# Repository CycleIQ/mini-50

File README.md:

# mini-50
A small 50A 48V e-bike controller

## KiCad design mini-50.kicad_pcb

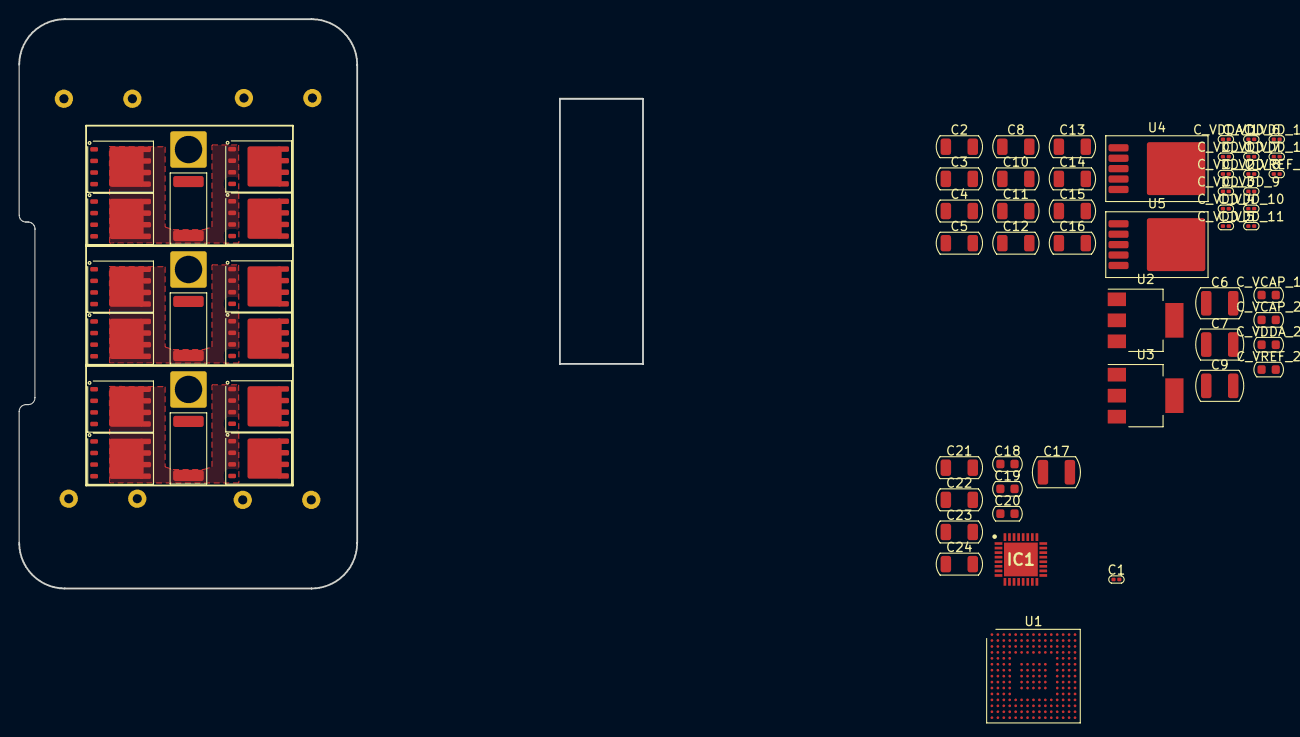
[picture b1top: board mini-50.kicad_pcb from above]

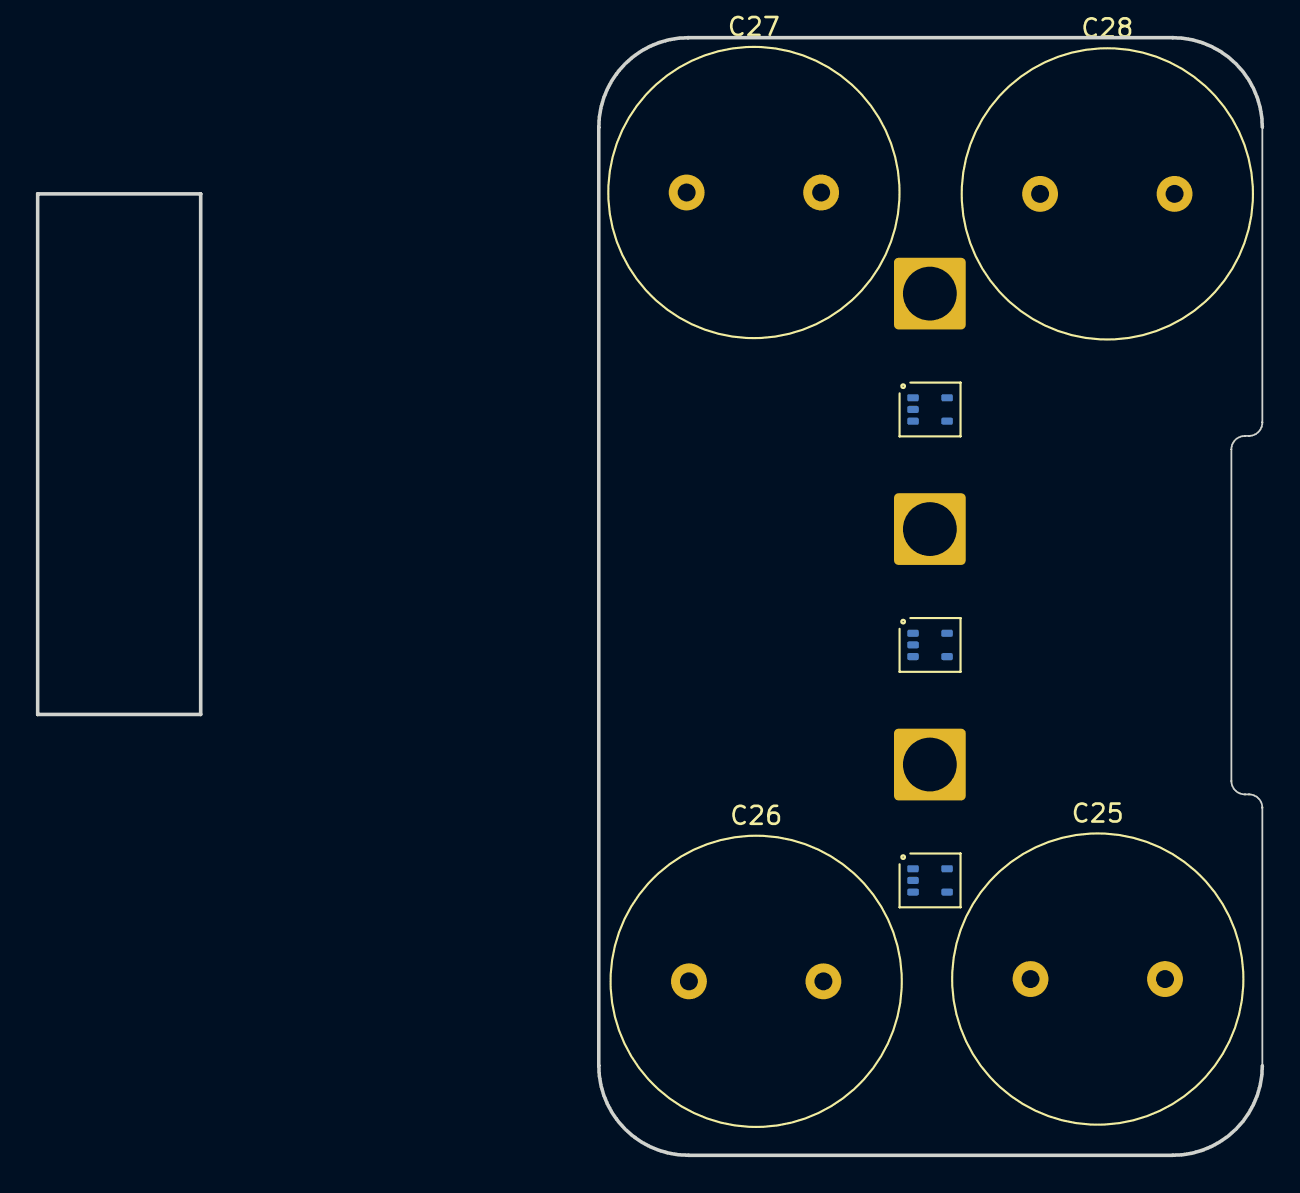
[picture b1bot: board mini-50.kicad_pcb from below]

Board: 4 copper layers, 74 parts (7 on the bottom side), 30 nets, no tracks yet.

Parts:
C1: 100nF; C_0201_0603Metric
C2, C5, C8, C10, C11, C12, C13, C14, C15, C16: 22uF/25V; C_1206_3216Metric
C3, C4: 4.7uF; C_1206_3216Metric
C6, C7, C9, C17: 10uF/100V; C_1210_3225Metric
C18: 1nF; C_0603_1608Metric
C19: 1uF; C_0603_1608Metric
C20: 10nF/25V; C_0603_1608Metric
C21: 10uF/25V; C_1206_3216Metric
C22, C23, C24: 2.2uF; C_1206_3216Metric
C25, C26, C27, C28: 680uF; C_Radial_D16.0mm_H25.0mm_P7.50mm
C_VCAP_1, C_VCAP_2: 2.2uF; C_0603_1608Metric
C_VDDA_1: 100nF; C_0201_0603Metric
C_VDDA_2: 1uF; C_0603_1608Metric
C_VDD_1, C_VDD_2, C_VDD_3, C_VDD_4, C_VDD_5, C_VDD_6, C_VDD_7, C_VDD_8, C_VDD_9, C_VDD_10, C_VDD_11, C_VDD_12, C_VDD_13: 100nF; C_0201_0603Metric
C_VREF_1: 100nF; C_0201_0603Metric
C_VREF_2: 1uF; C_0603_1608Metric
IC1: 6ED2742S01QXTMA1; QFN50P500X500X90-33N-D
J1: PHASE_A; SolderWire-2.5sqmm_1x01_D2.4mm_OD3.6mm
J2: PHASE_B; SolderWire-2.5sqmm_1x01_D2.4mm_OD3.6mm
J3: PHASE_C; SolderWire-2.5sqmm_1x01_D2.4mm_OD3.6mm
Q1, Q2, Q3, Q4, Q5, Q6, Q7, Q8, Q9, Q10, Q11, Q12: TPH1R306PL; Infineon_PG-TDSON-8
R7, R8, R9: 1m; R_2512_6332Metric
U1: STM32H753IIKx; UFBGA-201_10x10mm_Layout15x15_P0.65mm
U2, U3: LM1117MP-3.3; SOT-223-3_TabPin2
U4, U5: TO-252-5_TabPin3
U6, U7, U8: SOT-353_SC-70-5

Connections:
+3.3V: C3.1, C4.1, C_VDD_1.1, C_VDD_2.1, C_VDD_3.1, C_VDD_4.1, C_VDD_5.1, C_VDD_6.1, C_VDD_7.1, C_VDD_8.1, C_VDD_9.1, C_VDD_10.1, C_VDD_11.1, C_VDD_12.1, C_VDD_13.1, U1.C1 (VBAT), U1.C5 (VDD), U1.C6 (PDR_ON), U1.C7 (VDD), U1.C8 (VDD), U1.C9 (VDD), U1.F3 (VDD), U1.G3 (VDD), U1.G13 (VDD), U1.J12 (VDD), U1.J13 (VDD), U1.K4 (VDD), U1.N8 (VDD), U1.N9 (VDD), U1.N10 (VDD), U2.2 (VO)
+3.3VA: C_VDDA_1.1, C_VDDA_2.1, U1.R1 (VDDA), U3.2 (VO), U6.3 (VS), U7.3 (VS), U8.3 (VS)
+5V: C2.1, C5.1, C12.1, C14.1, U2.3 (VI), U3.3 (VI)
+12V: C8.1, C10.1, C11.1, C13.1, C15.1, C16.1, U5.1 (VIN)
/VCAP: C_VCAP_1.1, C_VCAP_2.1, U1.F13 (VCAP), U1.M10 (VCAP)
/VREF: C_VREF_1.1, C_VREF_2.1, U1.P1 (VREF+)
/bldc_driver/PHASE_A: C23.2, IC1.10 (VS1), Q7.1 (S), Q7.2 (S), Q7.3 (S), Q8.5 (D), Q11.1 (S), Q11.2 (S), Q11.3 (S), Q12.5 (D), R9.2, U8.4 (IN+)
/bldc_driver/PHASE_A_CONN: J1.1, R9.1, U8.5 (IN-)
/bldc_driver/PHASE_B: C24.2, IC1.14 (VS2), Q5.1 (S), Q5.2 (S), Q5.3 (S), Q6.5 (D), Q9.1 (S), Q9.2 (S), Q9.3 (S), Q10.5 (D), R8.2, U7.4 (IN+)
/bldc_driver/PHASE_B_CONN: J2.1, R8.1, U7.5 (IN-)
/bldc_driver/PHASE_C: C22.2, IC1.18 (VS3), Q1.1 (S), Q1.2 (S), Q1.3 (S), Q2.5 (D), Q3.1 (S), Q3.2 (S), Q3.3 (S), Q4.5 (D), R7.2, U6.4 (IN+)
/bldc_driver/PHASE_C_CONN: J3.1, R7.1, U6.5 (IN-)
GND: C1.2, C2.2, C3.2, C4.2, C6.2, C7.2, C8.2, C9.2, C10.2, C11.2, C12.2, C13.2, C14.2, C15.2, C16.2, C17.2, C18.2, C19.2, C21.2, C25.2, C26.2, C27.2, C28.2, C_VCAP_1.2, C_VCAP_2.2, C_VDD_1.2, C_VDD_2.2, C_VDD_3.2, C_VDD_4.2, C_VDD_5.2, C_VDD_6.2, C_VDD_7.2, C_VDD_8.2, C_VDD_9.2, C_VDD_10.2, C_VDD_11.2, C_VDD_12.2, C_VDD_13.2, C_VREF_1.2, C_VREF_2.2, IC1.6 (VSS), IC1.7 (ITRIP), IC1.8 (COM), Q2.1 (S), Q2.2 (S), Q2.3 (S), Q4.1 (S), Q4.2 (S), Q4.3 (S), Q6.1 (S), Q6.2 (S), Q6.3 (S), Q8.1 (S), Q8.2 (S), Q8.3 (S), Q10.1 (S), Q10.2 (S), Q10.3 (S), Q12.1 (S), Q12.2 (S), Q12.3 (S), U1.D5 (VSS), U1.D6 (BOOT0), U1.D7 (VSS), U1.D8 (VSS), U1.D9 (VSS), U1.F2 (VSS), U1.F6 (VSS), U1.F7 (VSS), U1.F8 (VSS), U1.F9 (VSS), U1.F10 (VSS), U1.F12 (VSS), U1.G2 (VSS), U1.G6 (VSS), U1.G7 (VSS), U1.G8 (VSS), U1.G9 (VSS), U1.G10 (VSS), U1.G12 (VSS), U1.H6 (VSS), U1.H7 (VSS), U1.H8 (VSS), U1.H9 (VSS), U1.H10 (VSS), U1.H12 (VSS), U1.J6 (VSS), U1.J7 (VSS), U1.J8 (VSS), U1.J9 (VSS), U1.J10 (VSS), U1.K6 (VSS), U1.K7 (VSS), U1.K8 (VSS), U1.K9 (VSS), U1.K10 (VSS), U1.L4 (VSS), U1.M8 (VSS), U1.M9 (VSS), U2.1 (GND), U4.3 (GND), U4.5 (EN), U5.3 (GND), U5.5 (EN)
GNDA: C5.2, C_VDDA_1.2, C_VDDA_2.2, U1.M1 (VSSA), U1.N1 (VREF-), U3.1 (GND), U6.2 (GND), U7.2 (GND), U8.2 (GND)
unnamed: C19.1, IC1.1 (BJT_DR), IC1.2 (VREG)
unnamed: C20.1, IC1.3 (CP1)
unnamed: C20.2, IC1.4 (CP2)
unnamed: IC1.11 (HO1), Q7.4 (G)
unnamed: IC1.15 (HO2), Q5.4 (G)
unnamed: IC1.19 (HO3), Q1.4 (G)
unnamed: IC1.12 (LO1), Q8.4 (G)
unnamed: IC1.16 (LO2), Q6.4 (G)
unnamed: IC1.20 (LO3), Q2.4 (G)
unnamed: C18.1, IC1.31 (RFE)
unnamed: C23.1, IC1.9 (VB1)
unnamed: C24.1, IC1.13 (VB2)
unnamed: C22.1, IC1.17 (VB3)
unnamed: C21.1, IC1.5 (VCC)
unnamed: C1.1, U1.J1 (NRST)
VCC: C6.1, C7.1, C9.1, C17.1, C25.1, C26.1, C27.1, C28.1, IC1.32 (VIN), Q1.5 (D), Q3.5 (D), Q5.5 (D), Q7.5 (D), Q9.5 (D), Q11.5 (D), U4.1 (VIN)

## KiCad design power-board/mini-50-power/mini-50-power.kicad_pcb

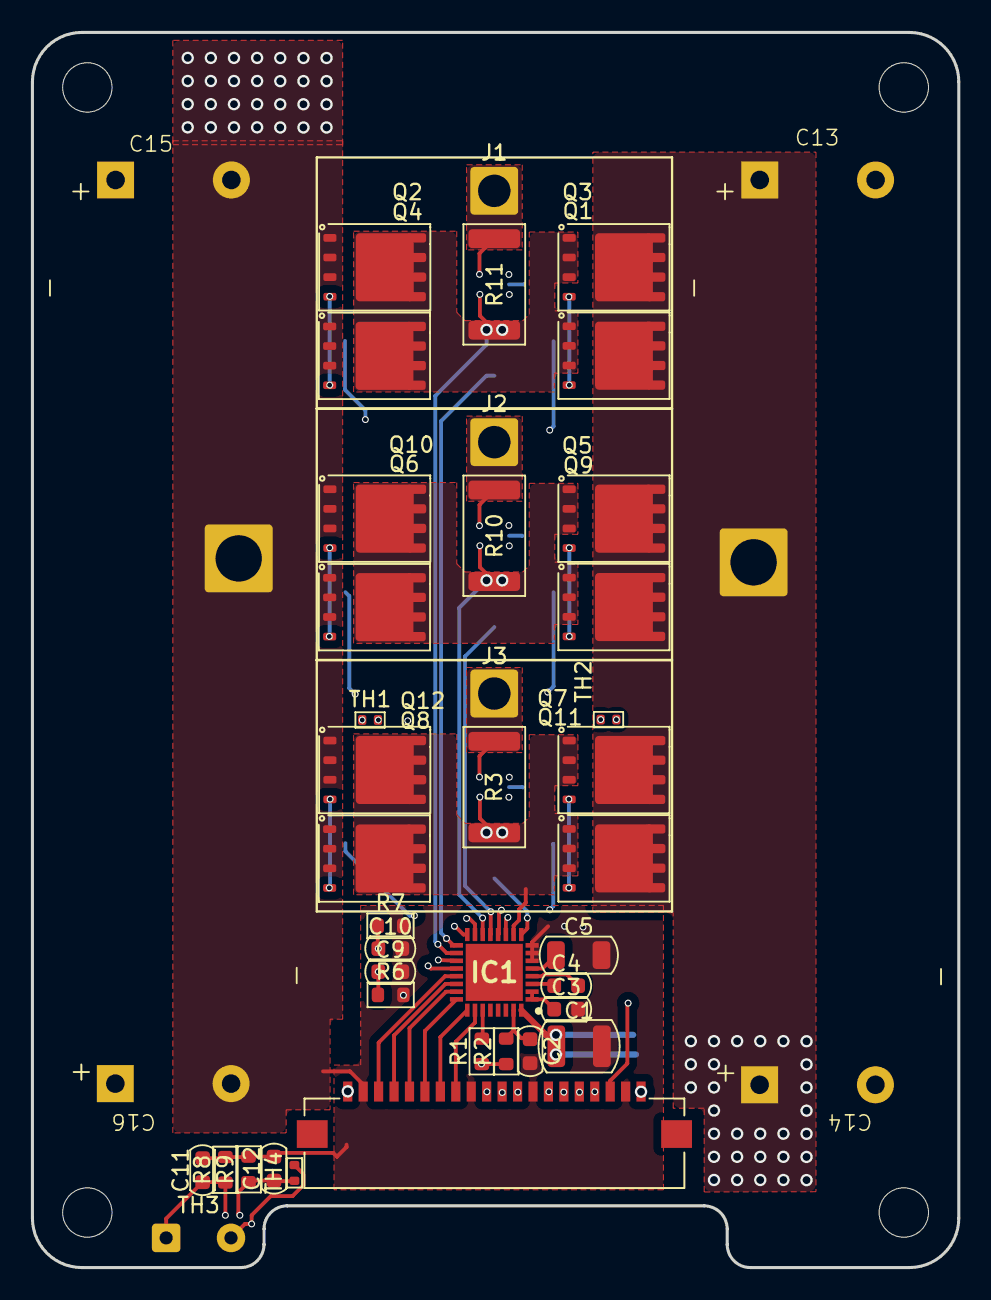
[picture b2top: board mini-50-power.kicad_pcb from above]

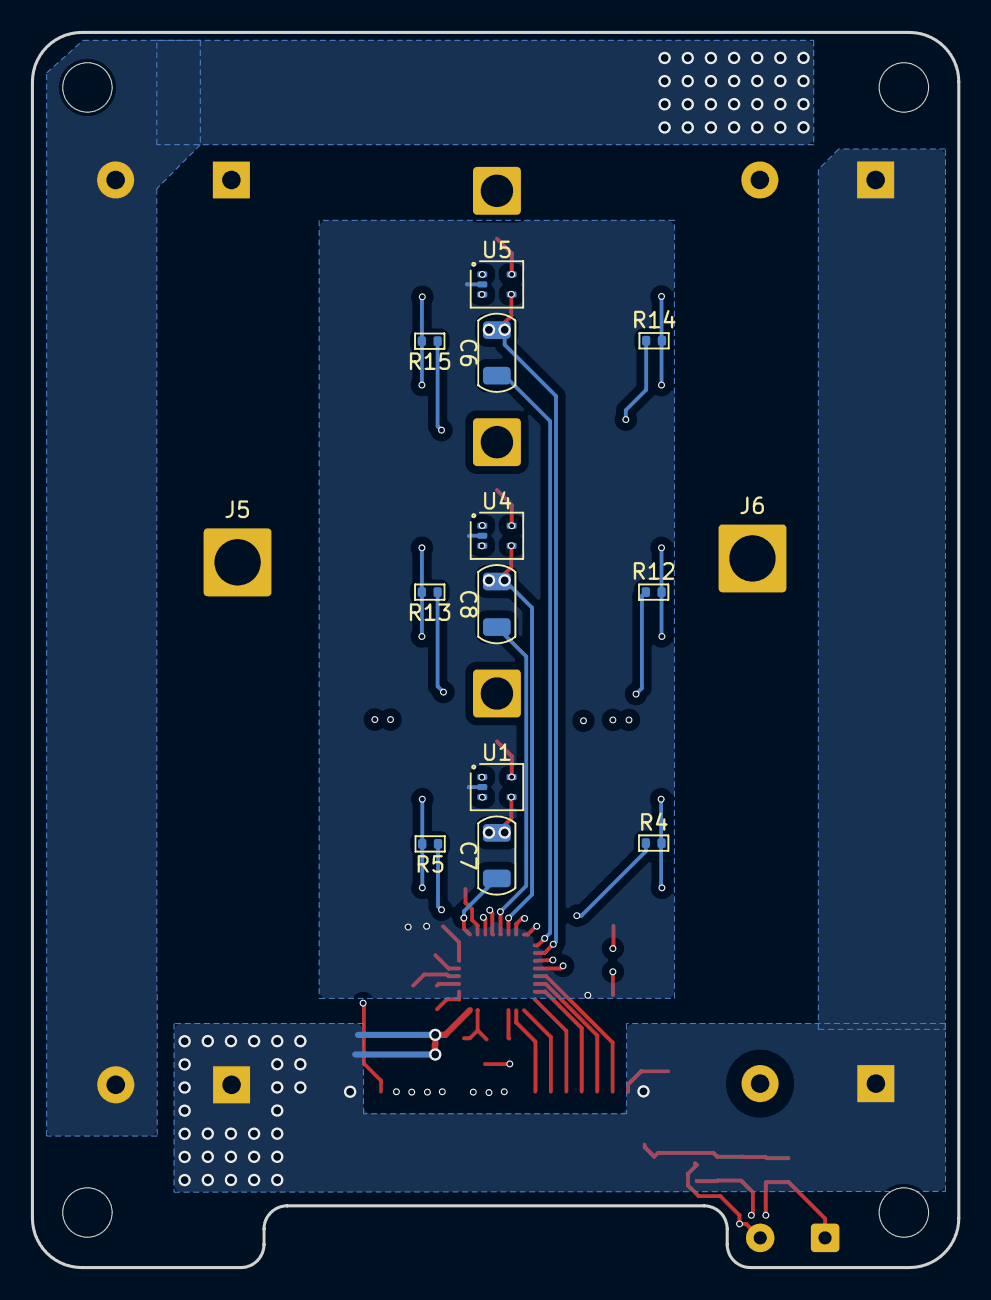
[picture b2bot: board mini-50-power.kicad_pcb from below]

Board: 4 copper layers, 60.0 x 80.0 mm, 57 parts (14 on the bottom side), 43 nets.

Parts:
C1: 10uF/100V; C_1210_3225Metric
C2: 1nF; C_0603_1608Metric
C3: 1uF; C_0603_1608Metric
C4: 10nF/25V; C_0603_1608Metric
C5: 10uF/25V; C_1206_3216Metric
C6, C7, C8: 2.2uF; C_1206_3216Metric
C9, C10, C11, C12: C; C_0603_1608Metric
C13, C15: 680uF; CAPACITOR_16mm_27mm
C14, C16: 680uF; CAPACITOR_16mm_27mm-reverse
IC1: 6ED2742S01QXTMA1; QFN50P500X500X90-33N-D
J1: PHASE_C; SolderWire-1.5sqmm_1x01_D1.7mm_OD3mm
J2: PHASE_B; SolderWire-1.5sqmm_1x01_D1.7mm_OD3mm
J3: PHASE_A; SolderWire-1.5sqmm_1x01_D1.7mm_OD3mm
J4: Conn_01x20; 686120148922
J5: BAT+; SolderWire-2.5sqmm_1x01_D2.4mm_OD4.4mm
J6: BAT-; SolderWire-2.5sqmm_1x01_D2.4mm_OD4.4mm
Q1, Q2, Q3, Q4, Q5, Q6, Q7, Q8, Q9, Q10, Q11, Q12: TPH1R306PL; Infineon_PG-TDSON-8
R1: 100k; R_0603_1608Metric
R2: 1M; R_0603_1608Metric
R3, R10, R11: 1m; R_2512_6332Metric
R4, R5, R12, R13, R14, R15: 22; R_0402_1005Metric
R6, R7, R8, R9: 10k; R_0603_1608Metric
TH1, TH2, TH4: Thermistor_NTC; R_0402_1005Metric
TH3: Thermistor_NTC; SolderWire-0.25sqmm_1x02_P4.2mm_D0.65mm_OD1.7mm
U1, U4, U5: SOT-353_SC-70-5

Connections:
+3.3V: J4.18, R1.1, R2.1, TH1.2, TH2.2, TH3.2, TH4.2, U1.3 (VS), U4.3 (VS), U5.3 (VS)
CS_A: J4.10, U1.1 (OUT)
CS_B: J4.11, U4.1 (OUT)
CS_C: J4.12, U5.1 (OUT)
GND: C1.2, C2.2, C3.2, C5.2, C9.2, C10.2, C11.2, C12.2, C13.2, C14.2, C15.2, C16.2, IC1.6 (VSS), IC1.7 (ITRIP), IC1.8 (COM), J4.2, J4.9, J4.13, J4.19, J6.1, Q2.1 (S), Q2.2 (S), Q2.3 (S), Q4.1 (S), Q4.2 (S), Q4.3 (S), Q6.1 (S), Q6.2 (S), Q6.3 (S), Q8.1 (S), Q8.2 (S), Q8.3 (S), Q10.1 (S), Q10.2 (S), Q10.3 (S), Q12.1 (S), Q12.2 (S), Q12.3 (S), R6.2, R7.2, R8.2, R9.2, U1.2 (GND), U4.2 (GND), U5.2 (GND)
HIN_A: IC1.26 (HIN1), J4.8
HIN_B: IC1.25 (HIN2), J4.7
HIN_C: IC1.24 (HIN3), J4.6
LIN_A: IC1.23 (LIN1), J4.5
LIN_B: IC1.22 (LIN2), J4.4
LIN_C: IC1.21 (LIN3), J4.3
unnamed: C3.1, IC1.1 (BJT_DR), IC1.2 (VREG)
unnamed: C4.1, IC1.3 (CP1)
unnamed: C4.2, IC1.4 (CP2)
unnamed: IC1.11 (HO1), R5.1
unnamed: IC1.15 (HO2), R13.1
unnamed: IC1.19 (HO3), R15.1
unnamed: IC1.27 (ITRIP_CONF), R1.2
unnamed: IC1.12 (LO1), R4.1
unnamed: IC1.16 (LO2), R12.1
unnamed: IC1.20 (LO3), R14.1
unnamed: C2.1, IC1.31 (RFE), R2.2
unnamed: C7.1, IC1.9 (VB1)
unnamed: C8.1, IC1.13 (VB2)
unnamed: C6.1, IC1.17 (VB3)
unnamed: C5.1, IC1.5 (VCC)
unnamed: Q1.4 (G), Q3.4 (G), R15.2
unnamed: Q2.4 (G), Q4.4 (G), R14.2
unnamed: Q5.4 (G), Q9.4 (G), R13.2
unnamed: Q6.4 (G), Q10.4 (G), R12.2
unnamed: Q7.4 (G), Q11.4 (G), R5.2
unnamed: Q8.4 (G), Q12.4 (G), R4.2
PHASE_A: C7.2, IC1.10 (VS1), Q7.1 (S), Q7.2 (S), Q7.3 (S), Q8.5 (D), Q11.1 (S), Q11.2 (S), Q11.3 (S), Q12.5 (D), R3.2, U1.4 (IN+)
PHASE_A_CONN: J3.1, R3.1, U1.5 (IN-)
PHASE_B: C8.2, IC1.14 (VS2), Q5.1 (S), Q5.2 (S), Q5.3 (S), Q6.5 (D), Q9.1 (S), Q9.2 (S), Q9.3 (S), Q10.5 (D), R10.2, U4.4 (IN+)
PHASE_B_CONN: J2.1, R10.1, U4.5 (IN-)
PHASE_C: C6.2, IC1.18 (VS3), Q1.1 (S), Q1.2 (S), Q1.3 (S), Q2.5 (D), Q3.1 (S), Q3.2 (S), Q3.3 (S), Q4.5 (D), R11.2, U5.4 (IN+)
PHASE_C_CONN: J1.1, R11.1, U5.5 (IN-)
TH_BOARD: C12.1, J4.17, R9.1, TH4.1
TH_DRIVER: C11.1, J4.16, R8.1, TH3.1
TH_HIGH: C10.1, J4.15, R7.1, TH2.1
TH_LOW: C9.1, J4.14, R6.1, TH1.1
VCC: C1.1, C13.1, C14.1, C15.1, C16.1, IC1.32 (VIN), J4.1, J4.20, J5.1, Q1.5 (D), Q3.5 (D), Q5.5 (D), Q7.5 (D), Q9.5 (D), Q11.5 (D)

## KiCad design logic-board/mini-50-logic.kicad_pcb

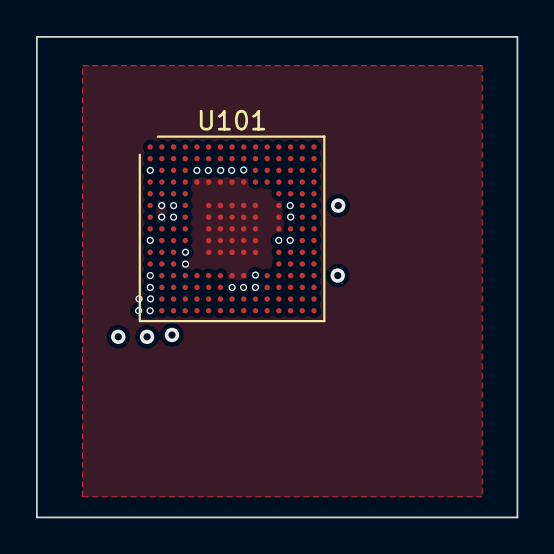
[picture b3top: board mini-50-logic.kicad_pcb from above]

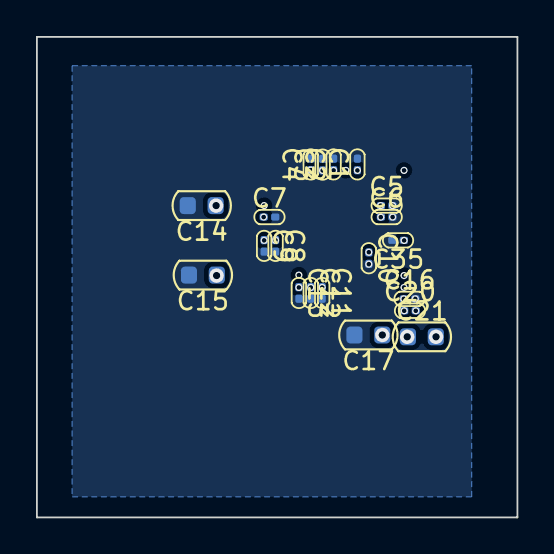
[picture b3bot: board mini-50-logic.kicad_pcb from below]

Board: 6 copper layers, 26.7 x 26.7 mm, 21 parts (20 on the bottom side), 7 nets.

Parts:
C1, C2, C3, C4, C5, C6, C7, C8, C9, C10, C11, C12, C13, C16, C20, C35: 100nF; C_0201_0603Metric
C14, C15: 2.2uF; C_0603_1608Metric
C17, C21: 1uF; C_0603_1608Metric
U101: STM32H753IIKx; UFBGA-201_10x10mm_Layout15x15_P0.65mm

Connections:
+3.3V: C1.1, C2.1, C3.1, C4.1, C5.1, C6.1, C7.1, C8.1, C9.1, C10.1, C11.1, C12.1, C13.1, U101.C1 (VBAT), U101.C5 (VDD), U101.C6 (PDR_ON), U101.C7 (VDD), U101.C8 (VDD), U101.C9 (VDD), U101.F3 (VDD), U101.G3 (VDD), U101.G13 (VDD), U101.J12 (VDD), U101.J13 (VDD), U101.K4 (VDD), U101.N8 (VDD), U101.N9 (VDD), U101.N10 (VDD)
GND: C1.2, C2.2, C3.2, C4.2, C5.2, C6.2, C7.2, C8.2, C9.2, C10.2, C11.2, C12.2, C13.2, C14.2, C15.2, C16.2, C17.2, C35.2, U101.D5 (VSS), U101.D6 (BOOT0), U101.D7 (VSS), U101.D8 (VSS), U101.D9 (VSS), U101.F2 (VSS), U101.F6 (VSS), U101.F7 (VSS), U101.F8 (VSS), U101.F9 (VSS), U101.F10 (VSS), U101.F12 (VSS), U101.G2 (VSS), U101.G6 (VSS), U101.G7 (VSS), U101.G8 (VSS), U101.G9 (VSS), U101.G10 (VSS), U101.G12 (VSS), U101.H6 (VSS), U101.H7 (VSS), U101.H8 (VSS), U101.H9 (VSS), U101.H10 (VSS), U101.H12 (VSS), U101.J6 (VSS), U101.J7 (VSS), U101.J8 (VSS), U101.J9 (VSS), U101.J10 (VSS), U101.K6 (VSS), U101.K7 (VSS), U101.K8 (VSS), U101.K9 (VSS), U101.K10 (VSS), U101.L4 (VSS), U101.M8 (VSS), U101.M9 (VSS)
GNDA: C20.2, C21.2, U101.M1 (VSSA), U101.N1 (VREF-)
unnamed: C35.1, U101.J1 (NRST)
VCAP: C14.1, C15.1, U101.F13 (VCAP), U101.M10 (VCAP)
VDDA: C20.1, C21.1, U101.R1 (VDDA)
VREF+: C16.1, C17.1, U101.P1 (VREF+)

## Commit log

2023-12-09 :books: Add license
2023-12-09 :tada: Init KiCad project
2023-12-09 :fire: Remove .lck file
2023-12-09 :wrench: Do not track .lck files
2023-12-09 :sparkles: Add STM32 to the schematic
2023-12-09 :wrench: Add autosave file to gitignore
2023-12-09 :sparkles: Add power management circuit for STM32
2023-12-09 :sparkles: Add 12V buck converter
2023-12-09 :sparkles: Add 5V buck converter
2023-12-10 :sparkles: Add 3.3V linear regulators
2023-12-28 ✨ Add initial bldc driver circuit
2024-01-16 📂 Commit before drastic power board changes
2024-11-16 🎉 Restart the project
